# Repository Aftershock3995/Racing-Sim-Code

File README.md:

#  `Pedal Controller Alpha Code`

This code is in early alpha; the app code has not been published, as well as the pedal code has not been updated to work with the app.

###  `Installation`
Download and install the Arduino IDE.
Connect the Teensy board to your computer.
Open the .ino file in the Arduino IDE.
Compile and upload the code to the board.
Connect the stepper motors, encoders, limit switches, and load cells to the appropriate pins on the board.

###  `To-Do`
- [X] `E-stop`
- [X] `Bluetooth`
- [X] `Ethernet`
- [X] `RTC`
- [X] `Status LED`
- [ ] `In-Game Overlay`
- [X] `Graph Line -> Force`

###  `In Progress`
- [X] `Pedal Position Line Threading`
- [X] `Line To Json Converting`
- [X] `EMMC Modules`

###  `Usage`
Not done 

###  `App early alpha preview`

<!--https://media.discordapp.net/attachments/868329637602816081/1112906816712609813/image.png-->

###  `PCB V3`

[comment]: <> (https://media.discordapp.net/attachments/868329637602816081/1152592707819143178/image.png)

###  `Credits`
This project was created by Aftershock.

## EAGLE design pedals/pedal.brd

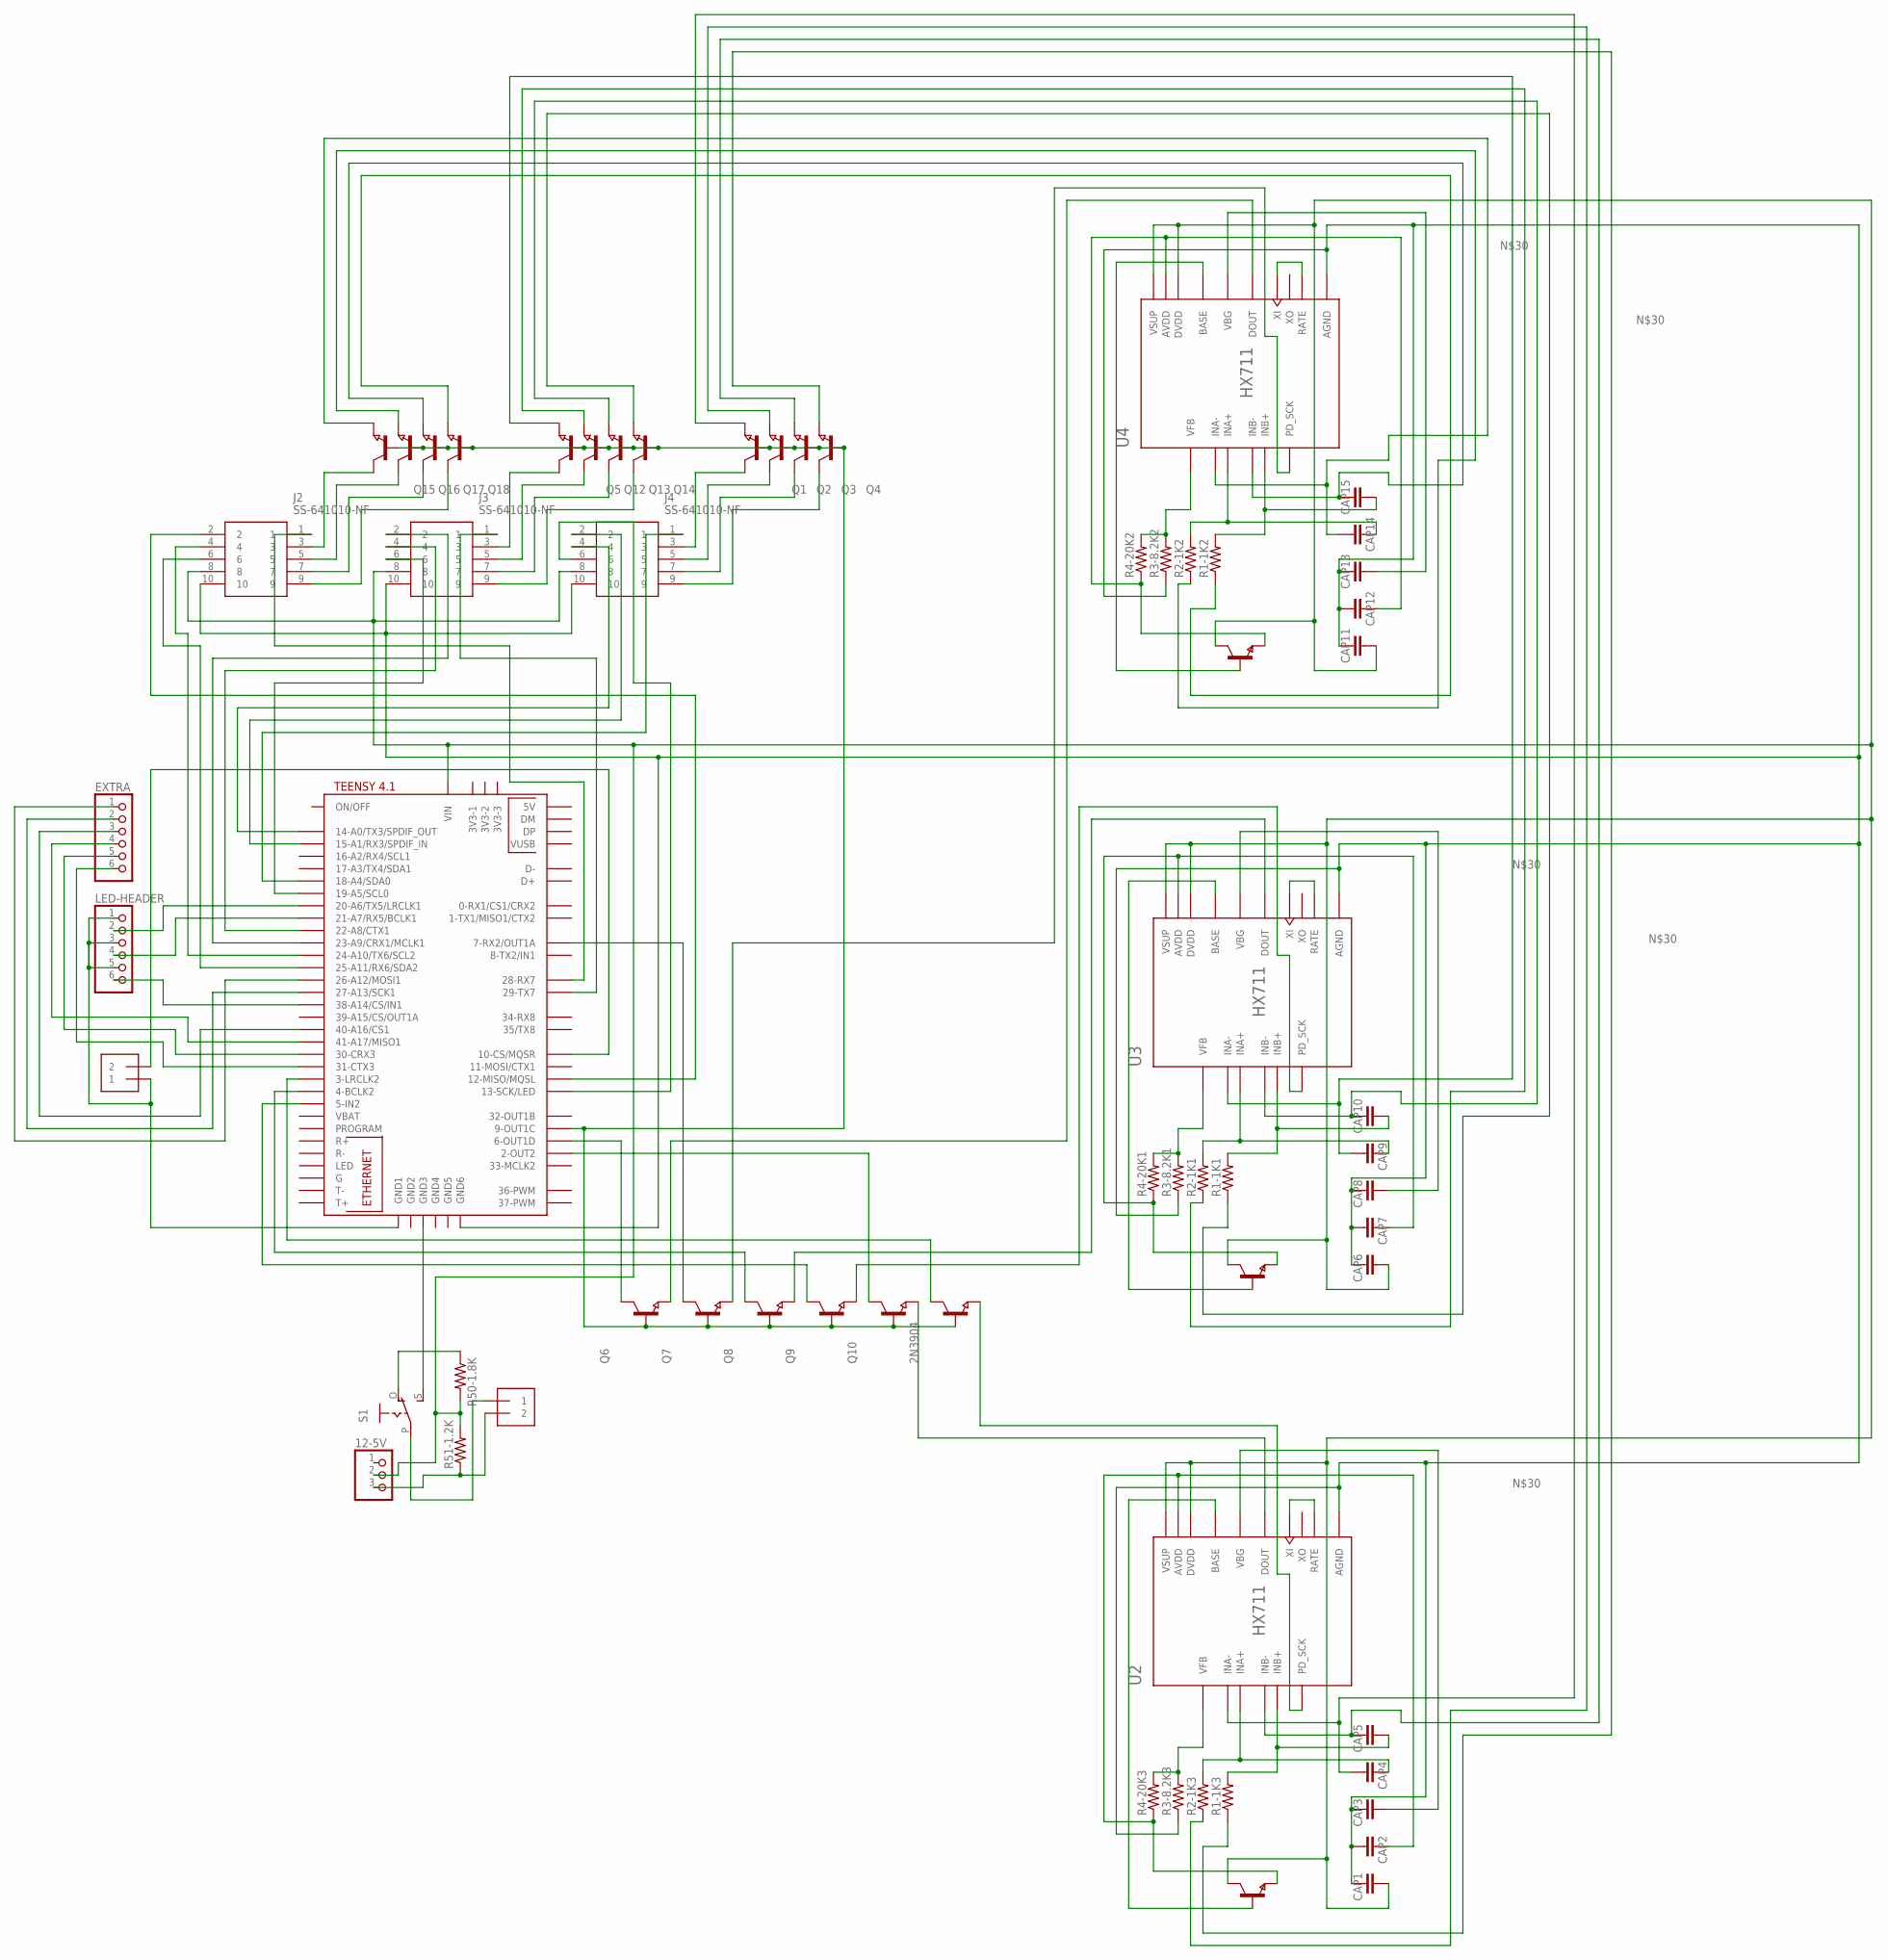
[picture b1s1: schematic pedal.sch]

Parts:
2N3904: NPN-TRANSISTOR_SOT23; SOT23
12-5V: PINHD-1X3; 1X03
CAP1, CAP2, CAP3, CAP6, CAP7, CAP8, CAP11, CAP12, CAP13: 1uf; 0603
CAP4, CAP5, CAP9, CAP10, CAP14, CAP15: .1uf; 0603
E-STOP: 1X2-3.5MM
EXTRA: PINHD-1X6B; 1X06-BIG
J2, J3, J4: SS-641010-NF
LED-HEADER: PINHD-1X6B; 1X06-BIG
POWER-IN: 1X2-3.5MM
Q1, Q2, Q3, Q4, Q5, Q6, Q7, Q8, Q9, Q10, Q12, Q13, Q14, Q15, Q16, Q17, Q18: NPN-TRANSISTOR_SOT23; SOT23
R1-1K1, R1-1K2, R1-1K3, R2-1K1, R2-1K2, R2-1K3, R3-8.2K1, R3-8.2K2, R3-8.2K3, R4-20K1, R4-20K2, R4-20K3, R50-1.8K, R51-1.2K: R-US_R0603; R0603
S1: EG1218S; EG1218
T1, T2, T3: 8550; SOT-23
U2, U3, U4: HX711; SOP127P600X180-16N
U$5: TEENSY41

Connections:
unnamed: CAP5.2, R1-1K3.2, U2.10 (INB+)
unnamed: CAP10.2, R1-1K1.2, U3.10 (INB+)
unnamed: CAP5.1, Q3.2 (E), U2.9 (INB-)
unnamed: Q4.2 (E), R1-1K3.1
unnamed: CAP4.2, R2-1K3.2, U2.8 (INA+)
unnamed: 2N3904.1 (B), Q1.1 (B), Q2.1 (B), Q3.1 (B), Q4.1 (B), Q5.1 (B), Q6.1 (B), Q7.1 (B), Q8.1 (B), Q9.1 (B), Q10.1 (B), Q12.1 (B), Q13.1 (B), Q14.1 (B), Q15.1 (B), Q16.1 (B), Q17.1 (B), Q18.1 (B), U$5.9-OUT1C
unnamed: Q2.2 (E), R2-1K3.1
unnamed: CAP3.2, U2.6 (VBG)
unnamed: R3-8.2K3.2, R4-20K3.2, U2.4 (VFB)
unnamed: 2N3904.2 (E), U2.11 (PD_SCK)
unnamed: T1.3 (B), U2.2 (BASE)
unnamed: U2.14 (XI), U2.15 (RATE)
unnamed: Q10.2 (E), U2.12 (DOUT)
unnamed: CAP10.1, Q13.2 (E), U3.9 (INB-)
unnamed: Q14.2 (E), R1-1K1.1
unnamed: CAP2.2, R4-20K3.1, T1.2 (E), U2.3 (AVDD)
unnamed: Q10.3 (C), U$5.2-OUT2
unnamed: 2N3904.3 (C), U$5.3-LRCLK2
unnamed: CAP9.2, R2-1K1.2, U3.8 (INA+)
unnamed: Q12.2 (E), R2-1K1.1
unnamed: CAP8.2, U3.6 (VBG)
unnamed: R3-8.2K1.2, R4-20K1.2, U3.4 (VFB)
unnamed: T2.3 (B), U3.2 (BASE)
unnamed: U3.14 (XI), U3.15 (RATE)
unnamed: Q9.3 (C), U$5.5-IN2
unnamed: CAP7.2, R4-20K1.1, T2.2 (E), U3.3 (AVDD)
unnamed: Q8.2 (E), U3.12 (DOUT)
unnamed: Q9.2 (E), U3.11 (PD_SCK)
unnamed: Q7.3 (C), U$5.7-RX2/OUT1A
unnamed: CAP1.1, CAP2.1, CAP3.1, CAP6.1, CAP7.1, CAP8.1, CAP11.1, CAP12.1, CAP13.1, J2.10, J3.10, J4.10, R3-8.2K1.1, R3-8.2K2.1, R3-8.2K3.1, U2.5 (AGND), U3.5 (AGND), U4.5 (AGND), U$5.GND6
unnamed: Q8.3 (C), U$5.4-BCLK2
unnamed: CAP9.1, Q5.2 (E), U3.7 (INA-)
unnamed: Q6.3 (C), U$5.6-OUT1D
unnamed: CAP4.1, Q1.2 (E), U2.7 (INA-)
unnamed: E-STOP.2, U$5.10-CS\MQSR (10-CS/MQSR)
unnamed: J4.6, U$5.13-SCK/LED
unnamed: E-STOP.1, LED-HEADER.1, LED-HEADER.3, LED-HEADER.5, U$5.GND1
unnamed: LED-HEADER.2, U$5.20-A6/TX5/LRCLK1
unnamed: 12-5V.2, CAP1.2, CAP6.2, CAP11.2, J2.8, J3.8, J4.8, R50-1.8K.2, R51-1.2K.2, T1.1 (C), T2.1 (C), T3.1 (C), U2.1 (VSUP), U2.16 (DVDD), U3.1 (VSUP), U3.16 (DVDD), U4.1 (VSUP), U4.16 (DVDD), U$5.VIN
unnamed: LED-HEADER.4, U$5.21-A7/RX5/BCLK1
unnamed: LED-HEADER.6, U$5.38-A14/CS/IN1
unnamed: J4.4, U$5.14-A0/TX3/SPDIF_OUT
unnamed: J4.2, U$5.15-A1/RX3/SPDIF_IN
unnamed: J4.1, U$5.18-A4/SDA0
unnamed: J3.6, U$5.19-A5/SCL0
unnamed: J3.4, U$5.22-A8/CTX1
unnamed: J3.2, U$5.23-A9/CRX1/MCLK1
unnamed: J3.1, U$5.29-TX7
unnamed: EXTRA.6, U$5.31-CTX3
unnamed: CAP15.2, R1-1K2.2, U4.10 (INB+)
unnamed: CAP15.1, Q17.2 (E), U4.9 (INB-)
unnamed: POWER-IN.1, S1.P
unnamed: S1.S, U$5.GND3
unnamed: 12-5V.3, POWER-IN.2, R51-1.2K.1
unnamed: Q18.2 (E), R1-1K2.1
unnamed: J2.1, U$5.28-RX7
unnamed: R50-1.8K.1, S1.O
unnamed: CAP14.2, R2-1K2.2, U4.8 (INA+)
unnamed: J2.6, U$5.25-A11/RX6/SDA2
unnamed: J2.4, U$5.24-A10/TX6/SCL2
unnamed: Q16.2 (E), R2-1K2.1
unnamed: EXTRA.5, U$5.30-CRX3
unnamed: J2.2, U$5.12-MISO/MQSL
unnamed: CAP13.2, U4.6 (VBG)
unnamed: R3-8.2K2.2, R4-20K2.2, U4.4 (VFB)
unnamed: T3.3 (B), U4.2 (BASE)
unnamed: U4.14 (XI), U4.15 (RATE)
unnamed: CAP12.2, R4-20K2.1, T3.2 (E), U4.3 (AVDD)
unnamed: Q6.2 (E), U4.12 (DOUT)
unnamed: Q7.2 (E), U4.11 (PD_SCK)
unnamed: EXTRA.4, U$5.41-A17/MISO1
unnamed: EXTRA.3, U$5.40-A16/CS1
unnamed: EXTRA.2, U$5.27-A13/SCK1
unnamed: CAP14.1, Q15.2 (E), U4.7 (INA-)
unnamed: EXTRA.1, U$5.26-A12/MOSI1
unnamed: J2.7, Q17.3 (C)
unnamed: J2.5, Q16.3 (C)
unnamed: J2.3, Q15.3 (C)
unnamed: J3.7, Q13.3 (C)
unnamed: J3.5, Q12.3 (C)
unnamed: J2.9, Q18.3 (C)
unnamed: J3.3, Q5.3 (C)
unnamed: J4.7, Q3.3 (C)
unnamed: J4.5, Q2.3 (C)
unnamed: J4.3, Q1.3 (C)
unnamed: J3.9, Q14.3 (C)
unnamed: J4.9, Q4.3 (C)

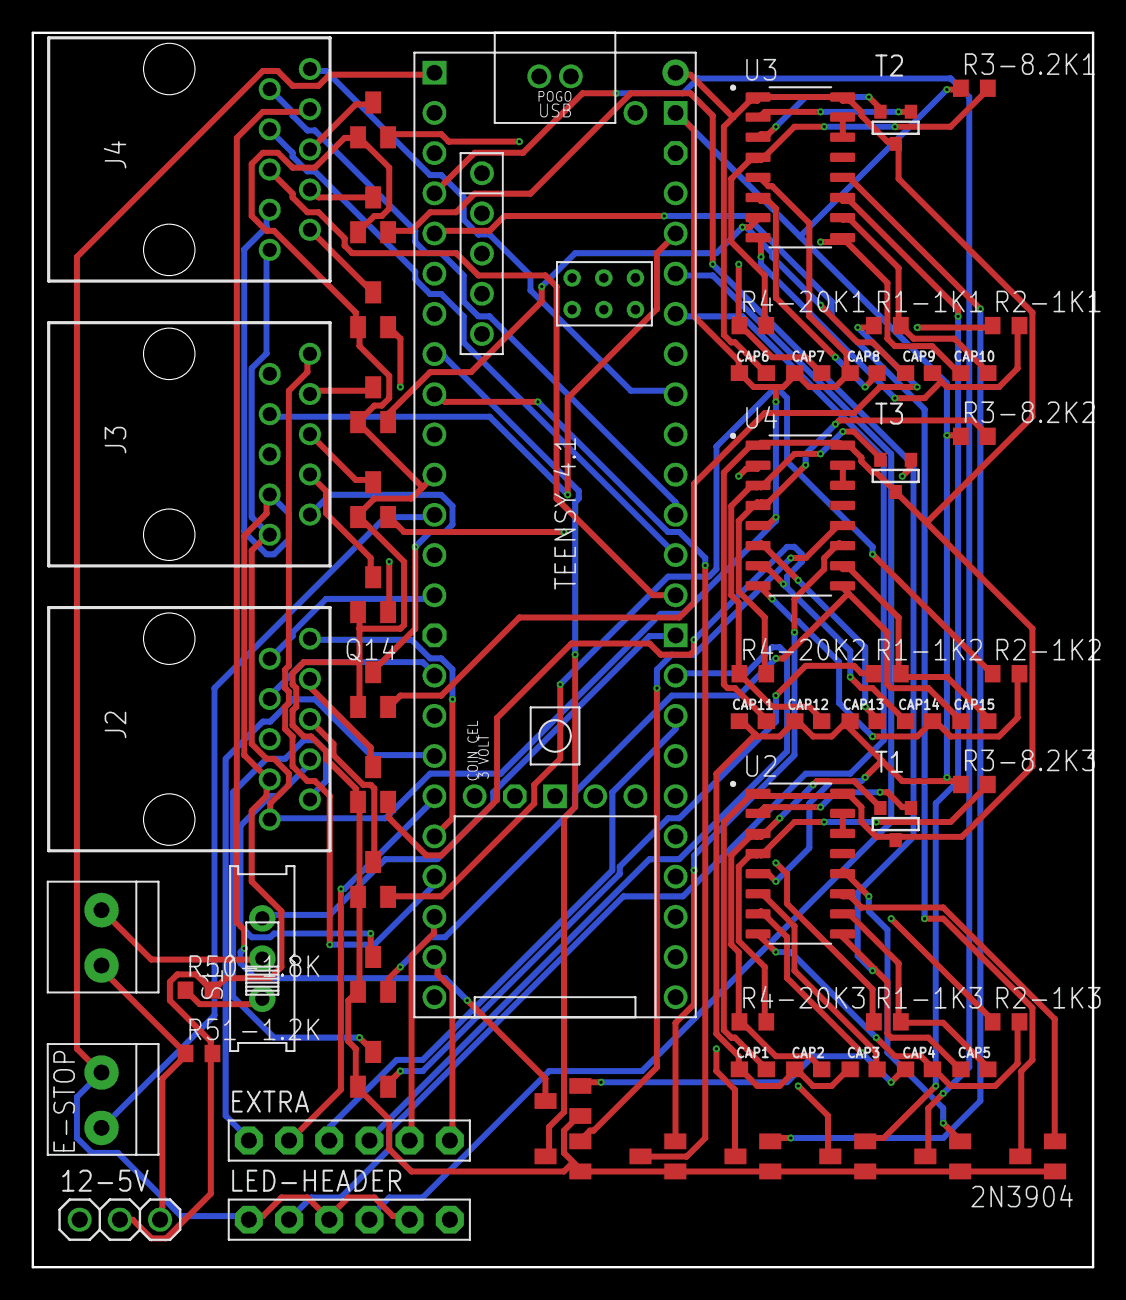
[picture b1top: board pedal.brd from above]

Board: 4 copper layers, 67.0 x 78.0 mm, 63 parts (0 on the bottom side), 87 nets.

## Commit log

2023-08-07 Add .gitattributes and .gitignore.
2023-08-07 Add project files.
2023-08-13 added pedal position line drawing currently not working
2023-08-14 Update README.md
    changed header images to be more rounded on the corners
2023-08-14 Fixing position line not tested
2023-08-19 update to line
2023-08-24 added fading to backround edited PedalDrawing to contain the position float (for easier chainging)
2023-08-25 test?
2023-08-25 updated local copy
2023-08-27 added looping position to the line
    desiredX += .5f;
    if (desiredX > 200f)
    {
    desiredX = 1f;
    })
2023-09-01 Serial int moves pedal line glitch with Invalidate(); making only 1 graph work
2023-09-01 all graphs have their own line glitch with line/border ghosting
2023-09-15 adding pedals 2 and 3
2023-09-15 added pedals 2 and 3 to the serial
2023-11-01 updating repo
2023-11-09 added pedal pcb file
2023-11-21 Rename MUX.md to MUX-Discontinued.md
2023-11-21 Rename MUX.ino to MUX-Discontinued.ino
2023-12-09 might have added force based on point and pedal location with cubic spline (who knows)
2023-12-28 Finished Interpolation
2024-01-01 fixed ffb curve handeling
2024-01-05 pushing changes

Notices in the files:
parts and their libraries:
SparkFun-Capacitors: Licensing: Creative Commons ShareAlike 4.0 International - https://creativecommons.org/licenses/by-sa/4.0
